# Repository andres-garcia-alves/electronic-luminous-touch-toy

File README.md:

# Luminous Touch Toy

Luminous Touch Toy made with NE555 IC and a piezo-electric sensor, with auto-off functionality.

&nbsp;

This project use the following electronic components:
- 1 x Integrated circuit NE555
- 1 x Piezo-electric sensor
- 4 x Multi-color LEDs
- 4 x 330 ohm resistors
- 1 x 10k ohm resistors
- 1 x 100k ohm resistor
- 1 x Transistor BC547 NPN
- 1 x Electrolitic capacitor 100uF 10v
- 1 x Switch-button
- 4 x Bateries 1.5v
- Some Empty Pen Tubes

The circuit:
- When pressing the toy surface it moves the empty pen tubes, making some presure on the piezo-electric.
- The piezo-electric generates some voltage on presure, activating the electronic circuit.
- The NE555 IC handles the 12 seconds enabled delay.

Notes:
- KiCad 6.0 schematic & PCB blueprints are also included.

&nbsp;

### Screenshots

| Diagram - Schematics                            | Diagram - PCB                                   |
|-------------------------------------------------|-------------------------------------------------|
|          |                |

| Diagram - PCB Render                            | Diagram - PCB Render                            |
|-------------------------------------------------|-------------------------------------------------|
|      |       |

| Prototype                                       | PCB Manufacturing                               |
|-------------------------------------------------|-------------------------------------------------|
|               |       |

| PCB Assembly                                    | Toy Assembly                                    |
|-------------------------------------------------|-------------------------------------------------|
|            |             |

| Project Final                                   | Project Final (YouTube video)                   |
|-------------------------------------------------|-------------------------------------------------|
|           |  |

See 'Rescources' sub-folder for more pictures & videos of the project.

&nbsp;

### Version History

v1.0 (2023.04.17) - Initial release.  

&nbsp;

This source code is licensed under GPL v3.0  
Please send me your feedback about this project: andres.garcia.alves@gmail.com

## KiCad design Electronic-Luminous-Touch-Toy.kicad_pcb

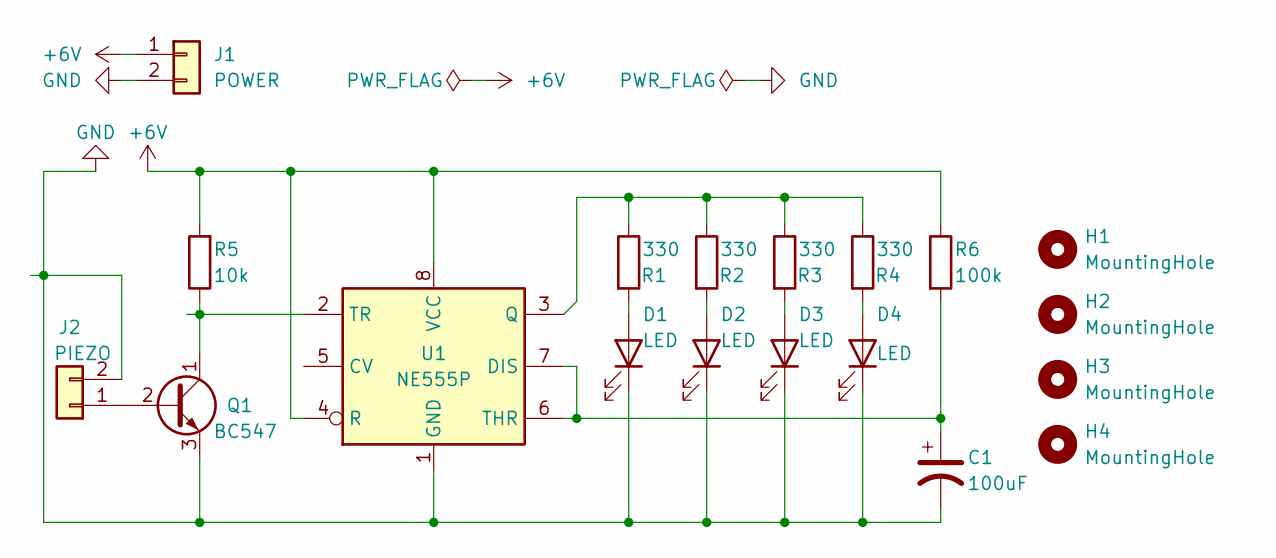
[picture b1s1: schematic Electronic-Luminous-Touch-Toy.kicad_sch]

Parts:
C1: 100uF; C_Radial_D8.0mm_H11.5mm_P3.50mm
D1, D2, D3, D4: LED; LED_D5.0mm
H1, H2, H3, H4: MountingHole; MountingHole_2.5mm
J1: POWER; PinHeader_1x02_P2.54mm_Horizontal
J2: PIEZO; PinHeader_1x02_P2.54mm_Horizontal
Q1: BC547; TO-92_Inline_Wide
R1, R2, R3, R4: 330; R_Axial_DIN0207_L6.3mm_D2.5mm_P10.16mm_Horizontal
R5: 10k; R_Axial_DIN0207_L6.3mm_D2.5mm_P10.16mm_Horizontal
R6: 100k; R_Axial_DIN0207_L6.3mm_D2.5mm_P10.16mm_Horizontal
U1: NE555P; DIP-8_W7.62mm

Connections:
+6V: J1.1, R5.2, R6.1, U1.4 (R), U1.8 (VCC)
GND: C1.2, D1.1 (K), D2.1 (K), D3.1 (K), D4.1 (K), J1.2, J2.2, Q1.3 (E), U1.1 (GND)
unnamed: C1.1, R6.2, U1.6 (THR), U1.7 (DIS)
unnamed: D1.2 (A), R1.2
unnamed: D2.2 (A), R2.2
unnamed: D3.2 (A), R3.2
unnamed: D4.2 (A), R4.2
unnamed: J2.1, Q1.2 (B)
unnamed: Q1.1 (C), R5.1, U1.2 (TR)
unnamed: R1.1, R2.1, R3.1, R4.1, U1.3 (Q)

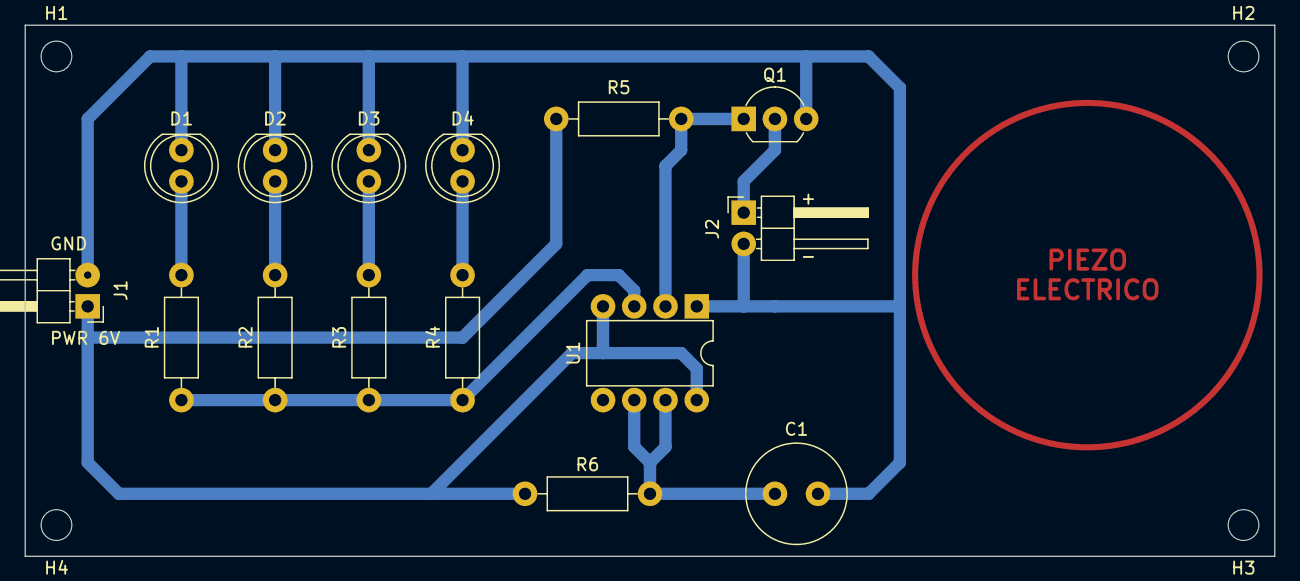
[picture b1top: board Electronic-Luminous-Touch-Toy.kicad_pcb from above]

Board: 2 copper layers, 101.6 x 43.2 mm, 19 parts (0 on the bottom side), 10 nets.

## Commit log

2023-04-17 Create LICENCE
2023-07-06 update Resources folder
